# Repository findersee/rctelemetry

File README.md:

# rctelemetry
<p>FrSky Smart port compatible Telemetry board.</p>

Telemetry features:<ul>
<li>Two DC power measurement channels, current and Voltage for speed controllers.</li>
<li>Battery input voltage measurement</li>
</ul>
Sbus integration:<ul>
  <li>2 servo channels</li>
  <li>2 PWM capable output channels 10A each</li>
  <li>2 PWM capable output channels 4A each</li>
  <li>2 Digital output channels 4A each</li>
  <li>2 Opto-isolated inputs</li>
  <li> Expansion UART </li>
</ul>

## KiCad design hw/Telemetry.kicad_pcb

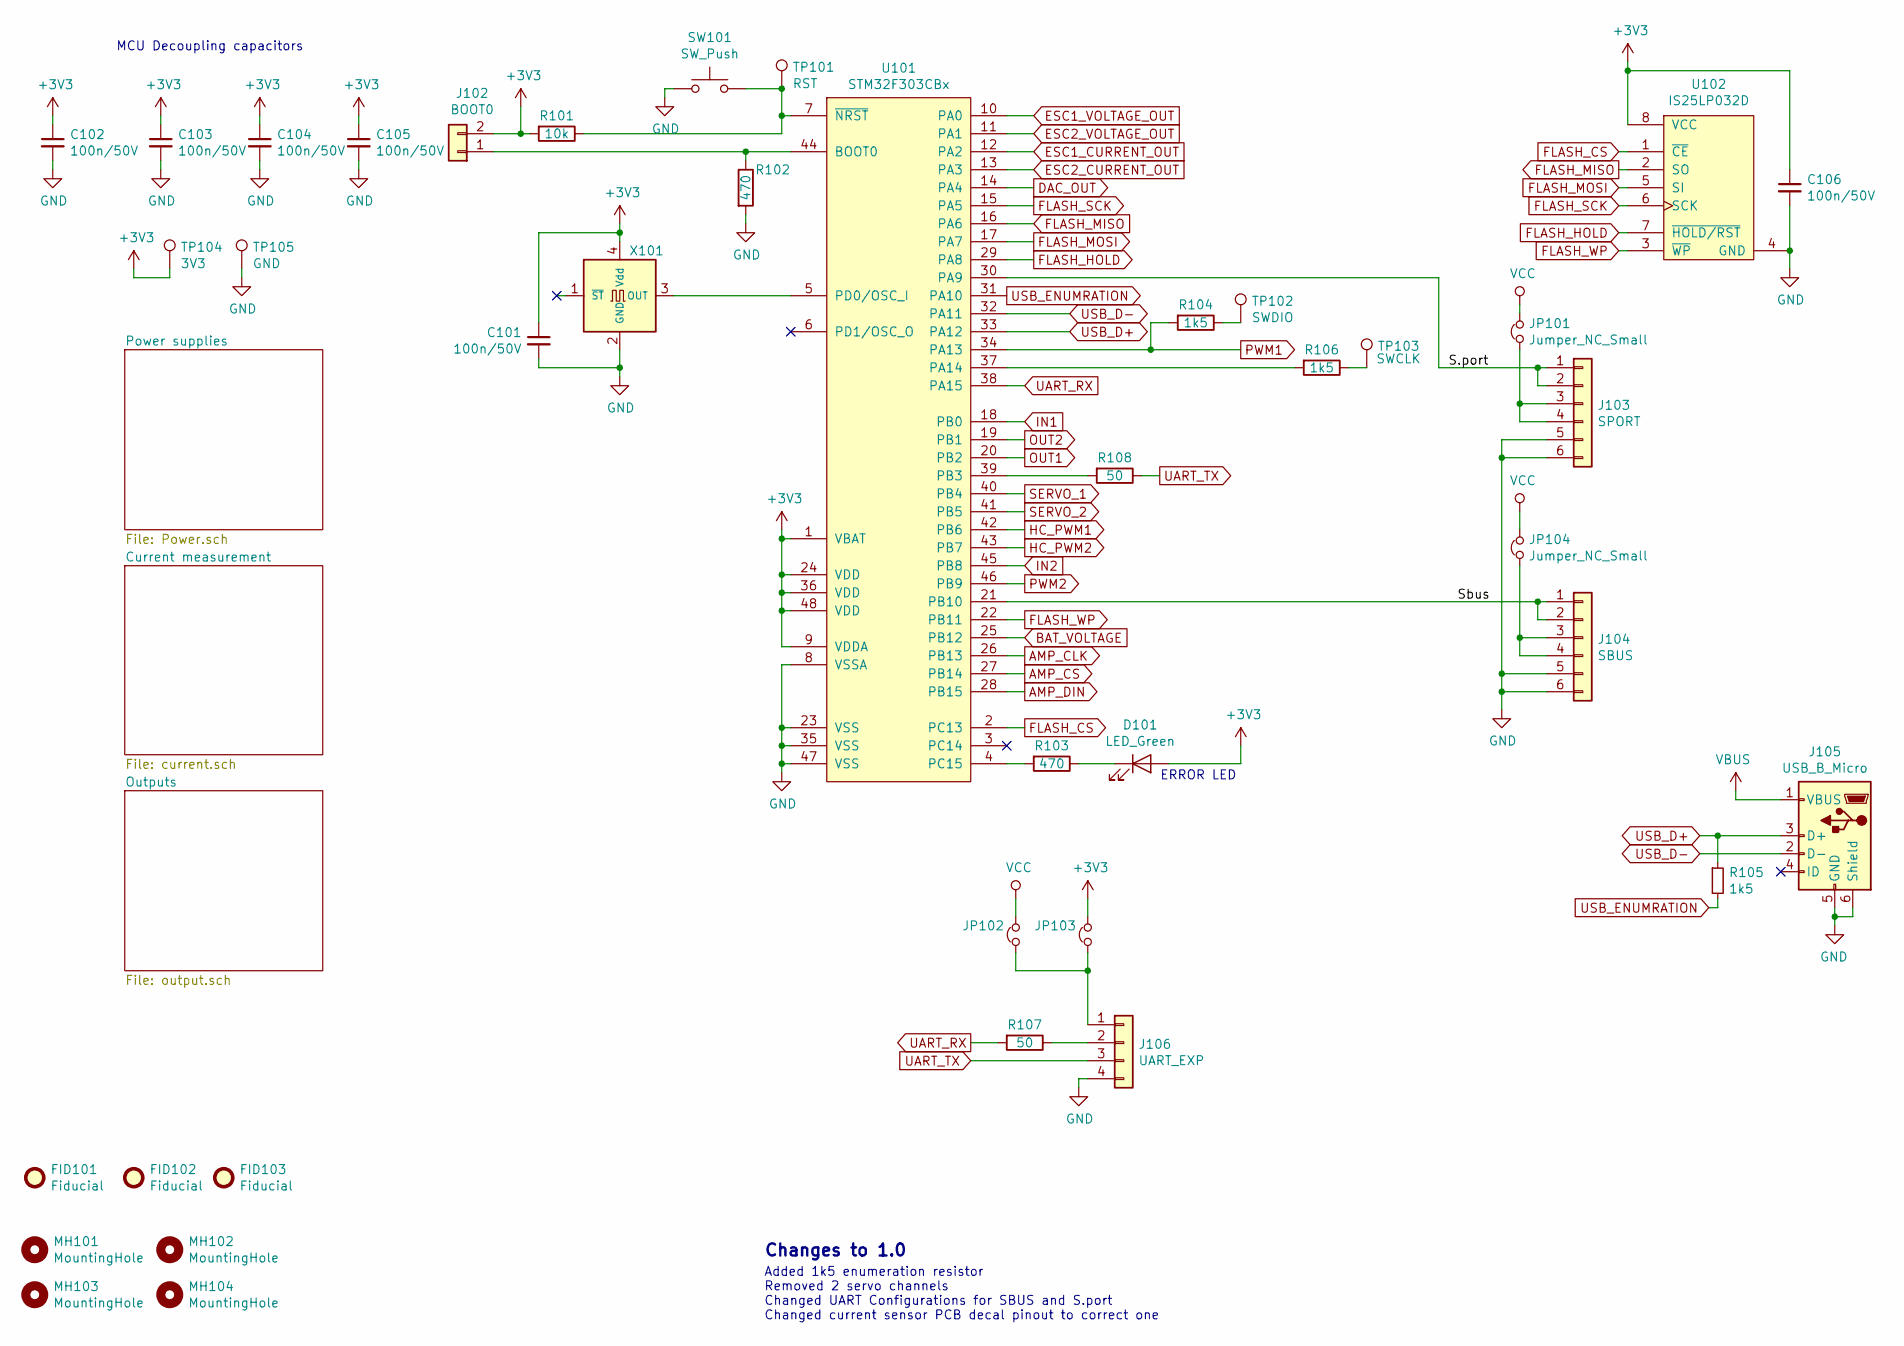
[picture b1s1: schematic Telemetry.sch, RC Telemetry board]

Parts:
C101, C102, C103, C104, C105, C106: 100n/50V; C_0603_1608Metric_Pad1.05x0.95mm_HandSolder
D101: LED_Green; LED_0603_HandSoldering
FID101, FID102, FID103: Fiducial; Fiducial_1mm_Mask2mm
J102: BOOT0; Pin_Header_Straight_1x02_Pitch1.27mm
J103: SPORT; Pin_Header_Straight_2x03
J104: SBUS; Pin_Header_Straight_2x03
J105: USB_B_Micro; USB_Micro-B
J106: UART_EXP; PinHeader_2x02_P2.54mm_Vertical
JP101, JP104: Jumper_NC_Small; PinHeader_1x02_P1.27mm_Vertical
JP102, JP103: Jumper_NC_Small; R_0402_1005Metric
MH101, MH102, MH103, MH104: MountingHole; MountingHole_3.2mm_M3_DIN965
R101: 10k; R_0603_1608Metric_Pad1.05x0.95mm_HandSolder
R102, R103: 470; R_0603_1608Metric_Pad1.05x0.95mm_HandSolder
R104, R105, R106: 1k5; R_0603_1608Metric_Pad1.05x0.95mm_HandSolder
R107, R108: 50; R_0603_1608Metric_Pad1.05x0.95mm_HandSolder
SW101: SW_Push; SW_SPST_B3U-1000P; MPN B3U-1000P
TP101: RST; SolderWirePad_single_0-8mmDrill
TP102: SWDIO; SolderWirePad_single_0-8mmDrill
TP103: SWCLK; SolderWirePad_single_0-8mmDrill
TP104: 3V3; SolderWirePad_single_0-8mmDrill
TP105: GND; SolderWirePad_single_0-8mmDrill
U101: STM32F303CBx; LQFP-48_7x7mm_Pitch0.5mm; MPN STM32F303CB
U102: IS25LP032D; SOIC-8_W5.6mm; MPN IS25LP032D
X101: SG-310_SCF_8.000000MHZ; SG- 310; MPN SG-310_SCF_8.000000MHZ

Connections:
+3V3: C101.1, C102.1, C103.1, C104.1, C105.1, C106.1, D101.2 (A), J102.2, JP103.2, R101.2, TP104.1, U101.1 (VBAT), U101.9 (VDDA), U101.24 (VDD), U101.36 (VDD), U101.48 (VDD), U102.8 (VCC), X101.4 (Vdd); also elsewhere on the board
/S.port: J103.1, J103.2, U101.30 (PA9)
/Sbus: J104.1, J104.2, U101.21 (PB10)
AMP_CLK: U101.26 (PB13); also elsewhere on the board
AMP_CS: U101.27 (PB14); also elsewhere on the board
AMP_DIN: U101.28 (PB15); also elsewhere on the board
BAT_VOLTAGE: U101.25 (PB12); also elsewhere on the board
DAC_OUT: U101.14 (PA4); also elsewhere on the board
ESC1_CURRENT_OUT: U101.12 (PA2); also elsewhere on the board
ESC1_VOLTAGE_OUT: U101.10 (PA0); also elsewhere on the board
ESC2_CURRENT_OUT: U101.13 (PA3); also elsewhere on the board
ESC2_VOLTAGE_OUT: U101.11 (PA1); also elsewhere on the board
FLASH_CS: U101.2 (PC13), U102.1 (~CE)
FLASH_HOLD: U101.29 (PA8), U102.7 (~HOLD/RST)
FLASH_MISO: U101.16 (PA6), U102.2 (SO)
FLASH_MOSI: U101.17 (PA7), U102.5 (SI)
FLASH_SCK: U101.15 (PA5), U102.6 (SCK)
FLASH_WP: U101.22 (PB11), U102.3 (~WP)
GND: C101.2, C102.2, C103.2, C104.2, C105.2, C106.2, J103.5, J103.6, J104.5, J104.6, J105.5 (GND), J105.6 (Shield), J106.4, R102.2, SW101.1, TP105.1, U101.8 (VSSA), U101.23 (VSS), U101.35 (VSS), U101.47 (VSS), U102.4 (GND), X101.2 (GND); also elsewhere on the board
HC_PWM1: U101.42 (PB6); also elsewhere on the board
HC_PWM2: U101.43 (PB7); also elsewhere on the board
IN1: U101.18 (PB0); also elsewhere on the board
IN2: U101.45 (PB8); also elsewhere on the board
unnamed: D101.1 (K), R103.1
unnamed: J102.1, R102.1, U101.44 (BOOT0)
unnamed: J103.3, J103.4, JP101.1
unnamed: J104.3, J104.4, JP104.1
unnamed: J106.1, JP102.1, JP103.1
unnamed: J106.2, R107.1
unnamed: R101.1, SW101.2, TP101.1, U101.7 (~NRST)
unnamed: R103.2, U101.4 (PC15)
unnamed: R104.1, TP102.1
unnamed: R106.1, TP103.1
unnamed: R106.2, U101.37 (PA14)
unnamed: R108.2, U101.39 (PB3)
unnamed: U101.5 (PD0/OSC_I), X101.3 (OUT)
OUT1: U101.20 (PB2); also elsewhere on the board
OUT2: U101.19 (PB1); also elsewhere on the board
PWM1: R104.2, U101.34 (PA13); also elsewhere on the board
PWM2: U101.46 (PB9); also elsewhere on the board
SERVO_1: U101.40 (PB4); also elsewhere on the board
SERVO_2: U101.41 (PB5); also elsewhere on the board
UART_RX: R107.2, U101.38 (PA15)
UART_TX: J106.3, R108.1
USB_D+: J105.3 (D+), R105.1, U101.33 (PA12)
USB_D-: J105.2 (D-), U101.32 (PA11)
USB_ENUMRATION: R105.2, U101.31 (PA10)
VBUS: J105.1 (VBUS)
VCC: JP101.2, JP102.2, JP104.2; also elsewhere on the board

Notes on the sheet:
ERROR LED
Changes to 1.0
MCU Decoupling capacitors
Added 1k5 enumeration resistor Removed 2 servo channels Changed UART Configurations for SBUS and S.port Changed current sensor PCB decal pinout to correct one

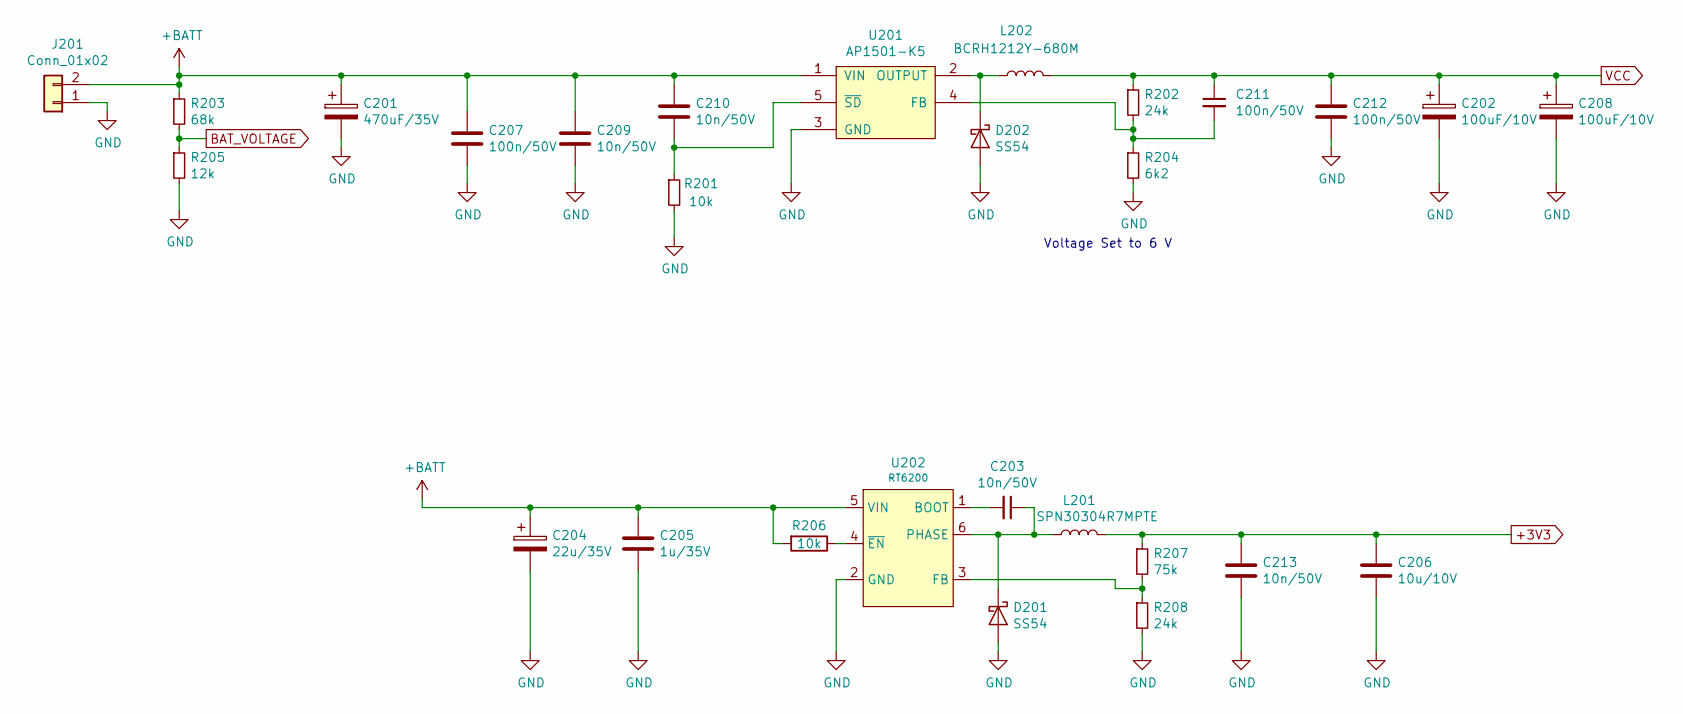
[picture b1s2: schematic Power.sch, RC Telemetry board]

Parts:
C201: 470uF/35V; CP_Radial_D10.0mm_P5.00mm
C202, C208: 100uF/10V; C_Radial_D7.5_L11.2_P2.5
C203, C213: 10n/50V; C_0603_1608Metric_Pad1.05x0.95mm_HandSolder
C204: 22u/35V; C_Radial_D7.5_L11.2_P2.5
C205: 1u/35V; C_0805_2012Metric_Pad1.15x1.40mm_HandSolder
C206: 10u/10V; C_0805_2012Metric_Pad1.15x1.40mm_HandSolder
C207, C211, C212: 100n/50V; C_0805_2012Metric_Pad1.15x1.40mm_HandSolder
C209, C210: 10n/50V; C_0805_2012Metric_Pad1.15x1.40mm_HandSolder
D201, D202: SS54; D_SMA_Handsoldering; MPN SS54
J201: Conn_01x02; 2Pin_4mm
L201: SPN30304R7MPTE; L_Sunlord_MWSA0402; MPN MWSA0402-4R7MT; LCSC Part-number C359291
L202: BCRH1212Y-680M; L_Sunlord_MWSA1206; MPN MWSA1206-470MT; LCSC Part-number C238002
R201, R206: 10k; R_0603_1608Metric_Pad1.05x0.95mm_HandSolder
R202, R208: 24k; R_0603_1608Metric_Pad1.05x0.95mm_HandSolder
R203: 68k; R_0603_1608Metric_Pad1.05x0.95mm_HandSolder
R204: 6k2; R_0603_1608Metric_Pad1.05x0.95mm_HandSolder
R205: 12k; R_0603_1608Metric_Pad1.05x0.95mm_HandSolder
R207: 75k; R_0603_1608Metric_Pad1.05x0.95mm_HandSolder
U201: AP1501-K5; TO-263-5_TabPin3; MPN AP1501-K5
U202: RT6200; SOT-23-6_Handsoldering; MPN RT6200

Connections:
+3V3: C206.1, C213.1, L201.2, R207.1; also elsewhere on the board
+BATT: C201.1, C204.1, C205.1, C207.1, C209.1, C210.1, J201.2, R203.1, R206.2, U201.1 (VIN), U202.5 (VIN); also elsewhere on the board
BAT_VOLTAGE: R203.2, R205.1; also elsewhere on the board
GND: C201.2, C202.2, C204.2, C205.2, C206.2, C207.2, C208.2, C209.2, C212.2, C213.2, D201.2 (A), D202.2 (A), J201.1, R201.2, R204.2, R205.2, R208.2, U201.3 (GND), U202.2 (GND); also elsewhere on the board
unnamed: C203.1, D201.1 (K), L201.1, U202.6 (PHASE)
unnamed: C203.2, U202.1 (BOOT)
unnamed: C210.2, R201.1, U201.5 (~SD)
unnamed: C211.2, R202.2, R204.1, U201.4 (FB)
unnamed: D202.1 (K), L202.1, U201.2 (OUTPUT)
unnamed: R206.1, U202.4 (~EN)
unnamed: R207.2, R208.1, U202.3 (FB)
VCC: C202.1, C208.1, C211.1, C212.1, L202.2, R202.1; also elsewhere on the board

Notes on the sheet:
Voltage Set to 6 V

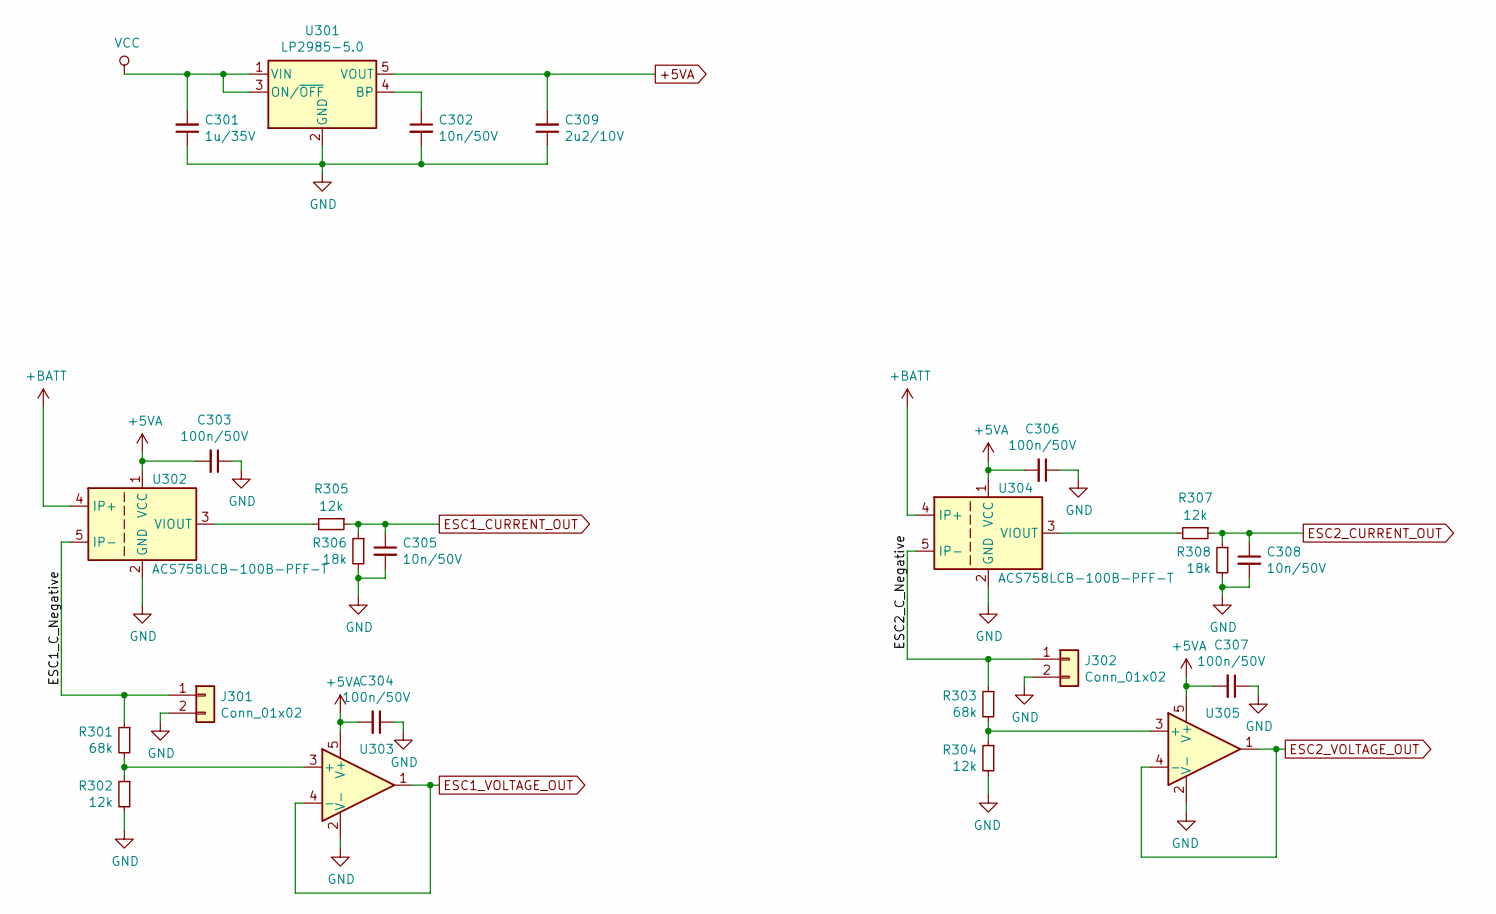
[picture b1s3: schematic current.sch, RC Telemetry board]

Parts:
C301: 1u/35V; C_0603_1608Metric_Pad1.05x0.95mm_HandSolder
C302, C305, C308: 10n/50V; C_0603_1608Metric_Pad1.05x0.95mm_HandSolder
C303, C304, C306, C307: 100n/50V; C_0603_1608Metric_Pad1.05x0.95mm_HandSolder
C309: 2u2/10V; C_0805_2012Metric_Pad1.15x1.40mm_HandSolder
J301, J302: Conn_01x02; 2Pin_4mm
R301, R303: 68k; R_0603_1608Metric_Pad1.05x0.95mm_HandSolder
R302, R304, R305, R307: 12k; R_0603_1608Metric_Pad1.05x0.95mm_HandSolder
R306, R308: 18k; R_0603_1608Metric_Pad1.05x0.95mm_HandSolder
U301: LP2985-5.0; SOT-23-5_HandSoldering; MPN LP2985-5.0
U302, U304: ACS758LCB-100B-PFF-T; Allegro_CB_PFF; MPN ACS758LCB-100B-PFF-T
U303, U305: MCP6001-OT; SOT-23-5_HandSoldering; MPN MCP6001-OT

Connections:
+5VA: C303.2, C304.2, C306.2, C307.2, C309.2, U301.5 (VOUT), U302.1 (VCC), U303.5 (V+), U304.1 (VCC), U305.5 (V+); also elsewhere on the board
+BATT: U302.4 (IP+), U304.4 (IP+); also elsewhere on the board
/Current measurement/ESC1_C_Negative: J301.1, R301.1, U302.5 (IP-)
/Current measurement/ESC2_C_Negative: J302.1, R303.1, U304.5 (IP-)
ESC1_CURRENT_OUT: C305.1, R305.1, R306.1; also elsewhere on the board
ESC1_VOLTAGE_OUT: U303.1, U303.4 (-); also elsewhere on the board
ESC2_CURRENT_OUT: C308.1, R307.1, R308.1; also elsewhere on the board
ESC2_VOLTAGE_OUT: U305.1, U305.4 (-); also elsewhere on the board
GND: C301.1, C302.2, C303.1, C304.1, C305.2, C306.1, C307.1, C308.2, C309.1, J301.2, J302.2, R302.2, R304.2, R306.2, R308.2, U301.2 (GND), U302.2 (GND), U303.2 (V-), U304.2 (GND), U305.2 (V-); also elsewhere on the board
unnamed: C302.1, U301.4 (BP)
unnamed: R301.2, R302.1, U303.3 (+)
unnamed: R303.2, R304.1, U305.3 (+)
unnamed: R305.2, U302.3 (VIOUT)
unnamed: R307.2, U304.3 (VIOUT)
VCC: C301.2, U301.1 (VIN), U301.3 (ON/~OFF~); also elsewhere on the board

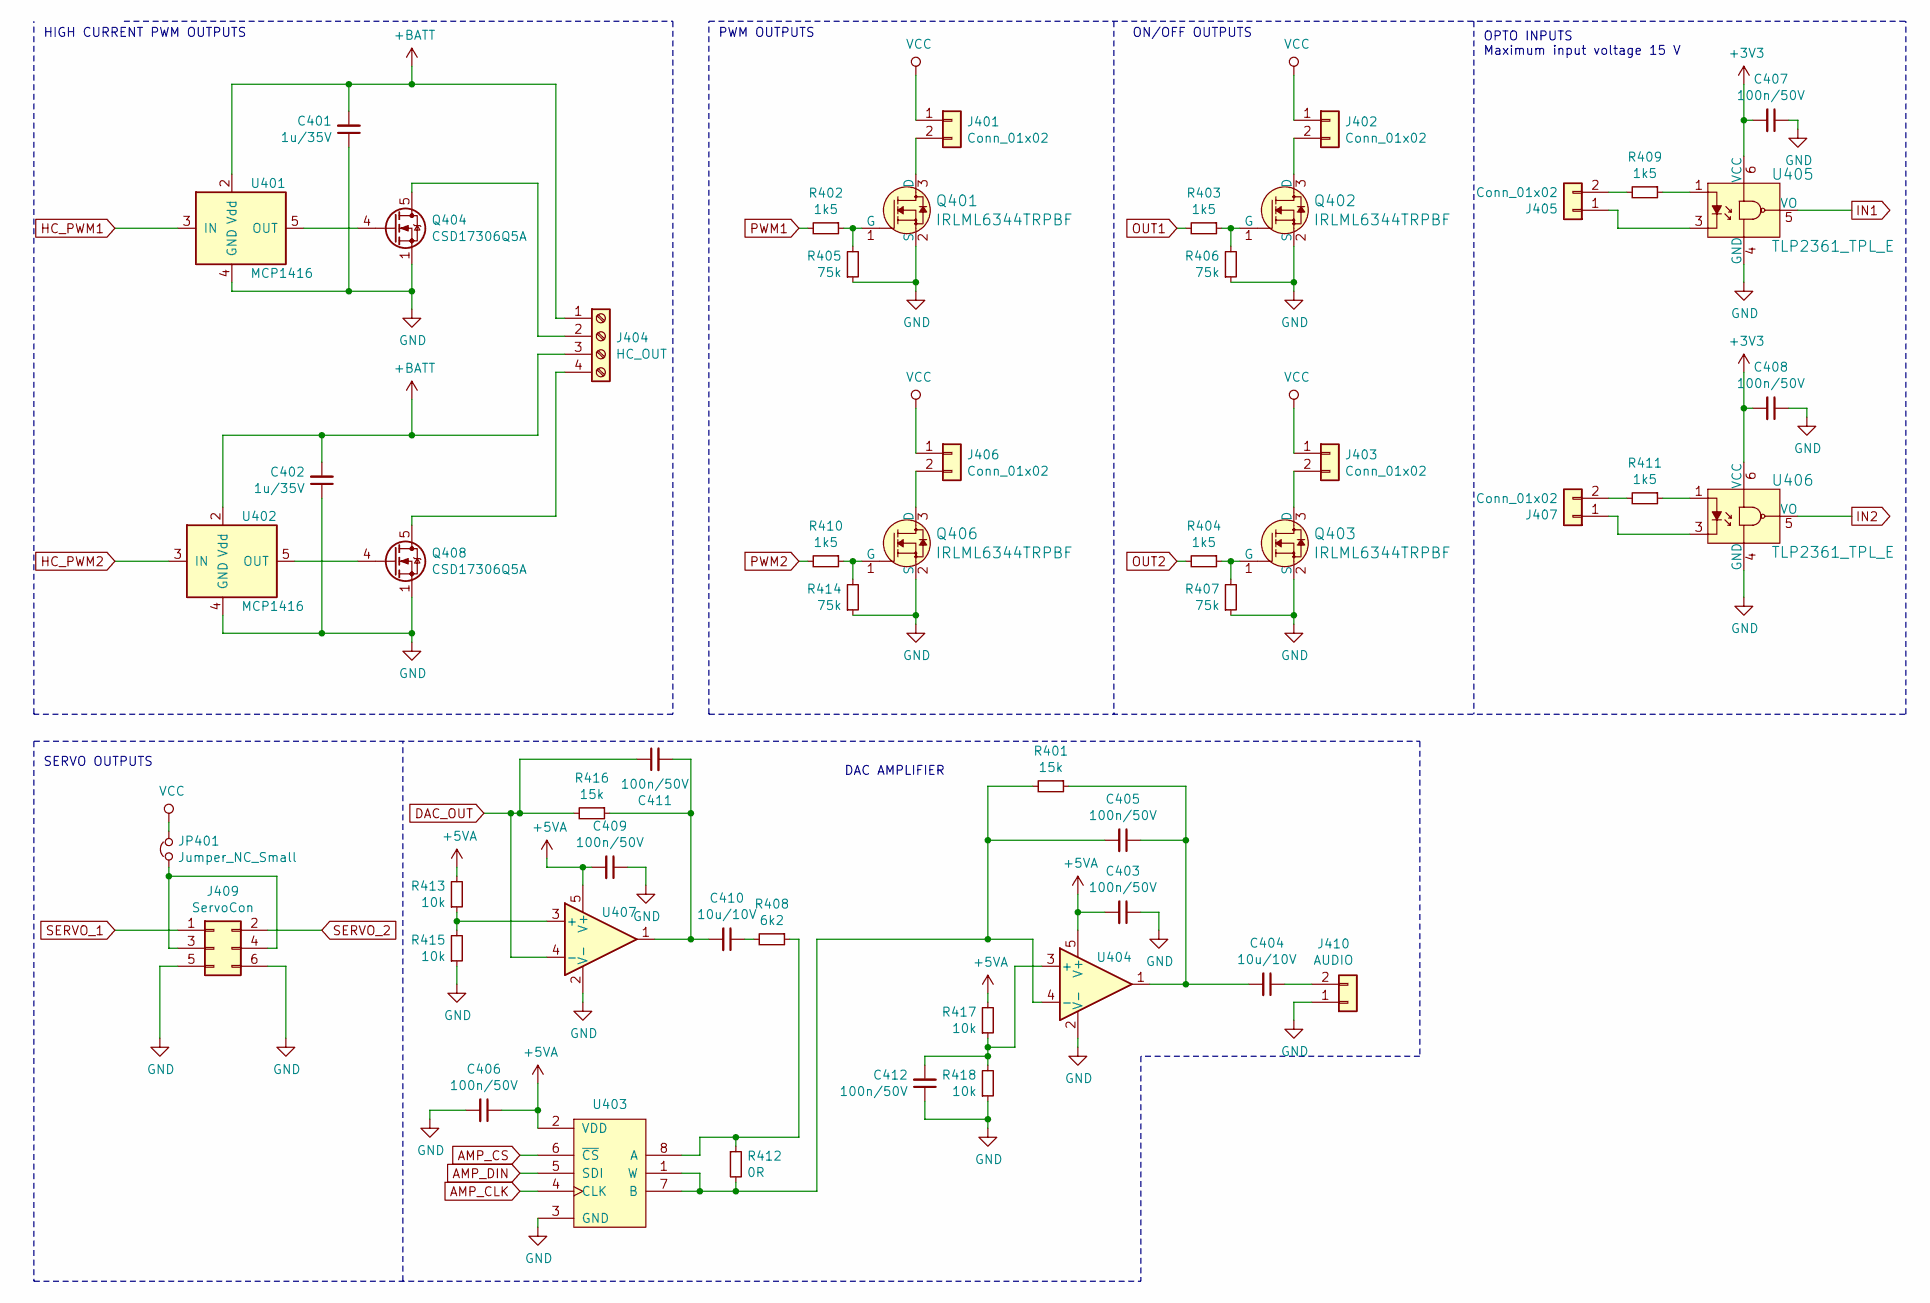
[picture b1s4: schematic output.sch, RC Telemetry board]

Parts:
C401, C402: 1u/35V; C_0805_2012Metric_Pad1.15x1.40mm_HandSolder
C403, C405, C406, C407, C408, C409, C411, C412: 100n/50V; C_0603_1608Metric_Pad1.05x0.95mm_HandSolder
C404, C410: 10u/10V; C_0603_1608Metric_Pad1.05x0.95mm_HandSolder
J401, J402, J403, J405, J406, J407: Conn_01x02; Molex_KK-254_AE-6410-02A_1x02_P2.54mm_Vertical
J404: HC_OUT; TerminalBlock_Phoenix_PT-1,5-4-5.0-H_1x04_P5.00mm_Horizontal
J409: ServoCon; PinHeader_2x03_P2.54mm_Vertical
J410: AUDIO; PinHeader_1x02_P2.54mm_Vertical
JP401: Jumper_NC_Small; PinHeader_1x02_P1.27mm_Vertical
Q401, Q402, Q403, Q406: IRLML6344TRPBF; SOT-23-3; MPN IRLML6344TRPBF; Digi-Key_PN IRLML6344TRPBFCT-ND
Q404, Q408: CSD17306Q5A; TDSON-8-1_HandSoldering; MPN CSD17306Q5A
R401, R416: 15k; R_0603_1608Metric_Pad1.05x0.95mm_HandSolder
R402, R403, R404, R409, R410, R411: 1k5; R_0603_1608Metric_Pad1.05x0.95mm_HandSolder
R405, R406, R407, R414: 75k; R_0603_1608Metric_Pad1.05x0.95mm_HandSolder
R408: 6k2; R_0603_1608Metric_Pad1.05x0.95mm_HandSolder
R412: 0R; R_0402_NoSilk
R413, R415, R417, R418: 10k; R_0603_1608Metric_Pad1.05x0.95mm_HandSolder
U401, U402: MCP1416; SOT-23-5_HandSoldering; MPN MCP1416
U403: AD5160BRJZ10-R2; SOT-23-8; MPN Analog Devices
U404, U407: MCP6001-OT; SOT-23-5_HandSoldering; MPN MCP6001-OT
U405, U406: TLP2361_TPL_E; SOIC-6-5_W4.55mm; MPN TLP2361-TPLECT; Digi-Key_PN TLP2361(TPLECT-ND

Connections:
+3V3: C407.2, C408.2, U405.6 (VCC), U406.6 (VCC); also elsewhere on the board
+5VA: C403.2, C406.1, C409.2, R413.2, R417.2, U403.2 (VDD), U404.5 (V+), U407.5 (V+); also elsewhere on the board
+BATT: C401.2, C402.2, J404.1, J404.3, U401.2 (Vdd), U402.2 (Vdd); also elsewhere on the board
AMP_CLK: U403.4 (CLK); also elsewhere on the board
AMP_CS: U403.6 (~CS); also elsewhere on the board
AMP_DIN: U403.5 (SDI); also elsewhere on the board
DAC_OUT: C411.1, R416.2, U407.4 (-); also elsewhere on the board
GND: C401.1, C402.1, C403.1, C406.2, C407.1, C408.1, C409.1, C412.1, J409.5, J409.6, J410.1, Q401.2 (S), Q402.2 (S), Q403.2 (S), Q404.1 (S), Q404.2 (S), Q404.3 (S), Q406.2 (S), Q408.1 (S), Q408.2 (S), Q408.3 (S), R405.1, R406.1, R407.1, R414.1, R415.1, R418.1, U401.4 (GND), U402.4 (GND), U403.3 (GND), U404.2 (V-), U405.4 (GND), U406.4 (GND), U407.2 (V-); also elsewhere on the board
HC_PWM1: U401.3 (IN); also elsewhere on the board
HC_PWM2: U402.3 (IN); also elsewhere on the board
IN1: U405.5 (VO); also elsewhere on the board
IN2: U406.5 (VO); also elsewhere on the board
unnamed: C404.1, J410.2
unnamed: C404.2, C405.1, R401.1, U404.1
unnamed: C405.2, R401.2, R412.2, U403.1 (W), U403.7 (B), U404.4 (-)
unnamed: C410.1, R408.2
unnamed: C410.2, C411.2, R416.1, U407.1
unnamed: C412.2, R417.1, R418.2, U404.3 (+)
unnamed: J401.2, Q401.3 (D)
unnamed: J402.2, Q402.3 (D)
unnamed: J403.2, Q403.3 (D)
unnamed: J404.2, Q404.5 (D)
unnamed: J404.4, Q408.5 (D)
unnamed: J405.1, U405.3
unnamed: J405.2, R409.2
unnamed: J406.2, Q406.3 (D)
unnamed: J407.1, U406.3
unnamed: J407.2, R411.2
unnamed: J409.3, J409.4, JP401.1
unnamed: Q401.1 (G), R402.1, R405.2
unnamed: Q402.1 (G), R403.1, R406.2
unnamed: Q403.1 (G), R404.1, R407.2
unnamed: Q404.4 (G), U401.5 (OUT)
unnamed: Q406.1 (G), R410.1, R414.2
unnamed: Q408.4 (G), U402.5 (OUT)
unnamed: R408.1, R412.1, U403.8 (A)
unnamed: R409.1, U405.1
unnamed: R411.1, U406.1
unnamed: R413.1, R415.2, U407.3 (+)
OUT1: R403.2; also elsewhere on the board
OUT2: R404.2; also elsewhere on the board
PWM1: R402.2; also elsewhere on the board
PWM2: R410.2; also elsewhere on the board
SERVO_1: J409.1; also elsewhere on the board
SERVO_2: J409.2; also elsewhere on the board
VCC: J401.1, J402.1, J403.1, J406.1, JP401.2; also elsewhere on the board

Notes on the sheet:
DAC AMPLIFIER
HIGH CURRENT PWM OUTPUTS
PWM OUTPUTS
ON/OFF OUTPUTS
SERVO OUTPUTS
OPTO INPUTS Maximum input voltage 15 V

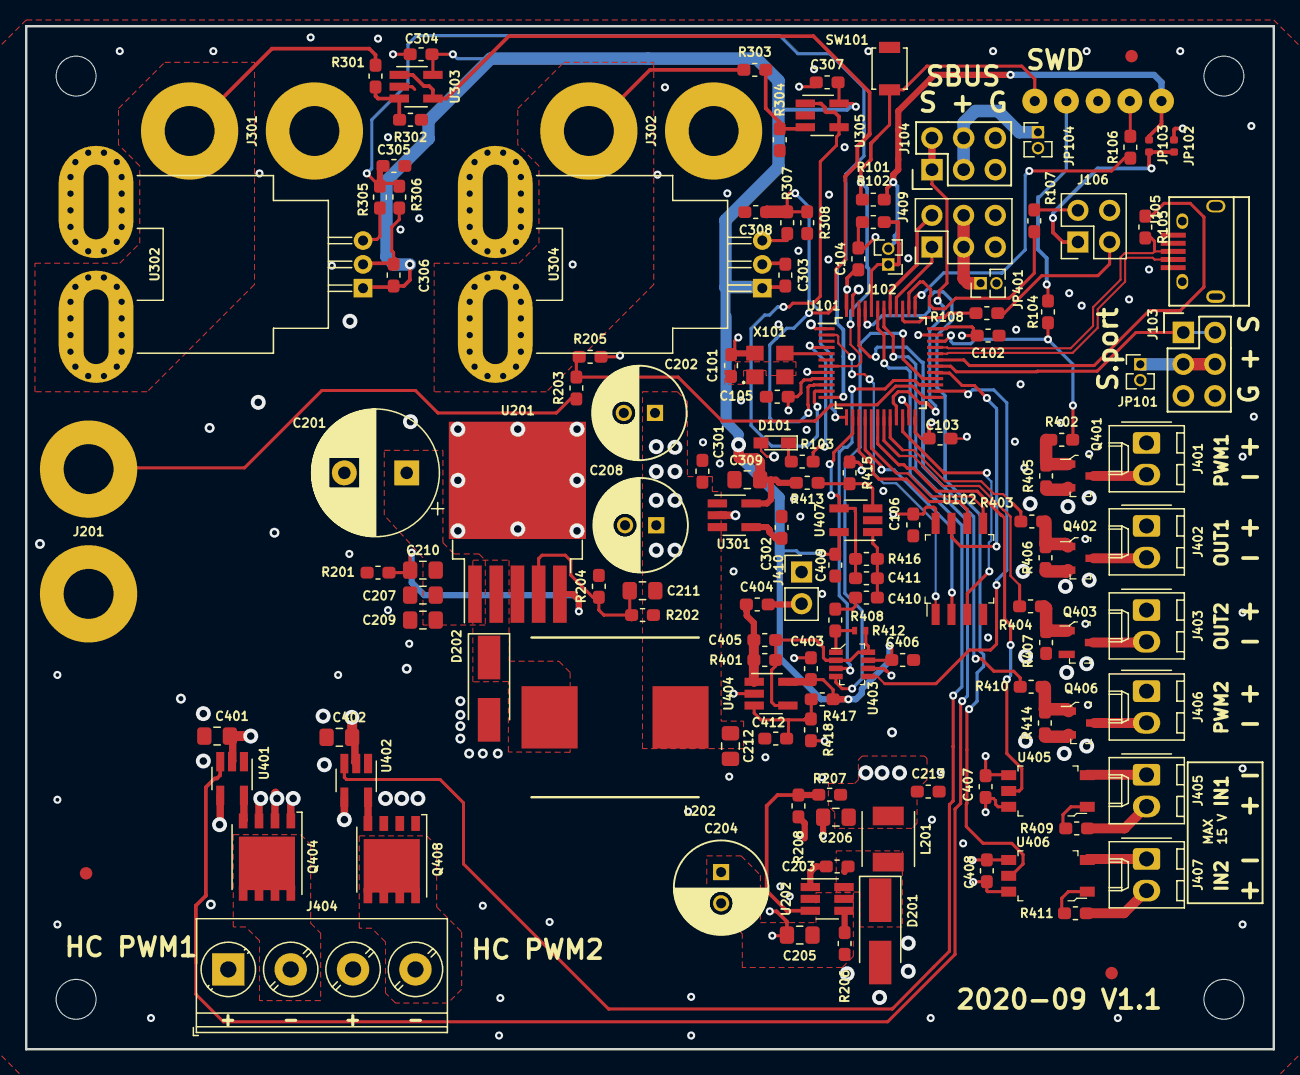
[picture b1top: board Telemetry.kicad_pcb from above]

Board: 4 copper layers, 100.0 x 82.0 mm, 146 parts (1 on the bottom side), 91 nets.

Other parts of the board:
https://github.com/findersee/rctelemetry: rctelemetry_QR

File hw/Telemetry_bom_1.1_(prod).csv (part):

Component,Description,Designator,Comment,Footprint,Quantity Per PCB,Datasheet,MPN,Manufacturer
1,"Unpolarized capacitor, small symbol",C101,100n/50V,0603_C,1,~,,
2,"Unpolarized capacitor, small symbol",C102,100n/50V,0603_C,1,~,,
3,"Unpolarized capacitor, small symbol",C103,100n/50V,0603_C,1,~,,
4,"Unpolarized capacitor, small symbol",C104,100n/50V,0603_C,1,~,,
5,"Unpolarized capacitor, small symbol",C105,100n/50V,0603_C,1,~,,
6,"Unpolarized capacitor, small symbol",C106,100n/50V,0603_C,1,~,,
7,Unpolarized capacitor,C207,100n/50V,0805_C,1,~,,
8,"Unpolarized capacitor, small symbol",C211,100n/50V,0805_C,1,~,,
9,Unpolarized capacitor,C212,100n/50V,0805_C,1,~,,
10,"Unpolarized capacitor, small symbol",C303,100n/50V,0603_C,1,~,,
11,"Unpolarized capacitor, small symbol",C304,100n/50V,0603_C,1,~,,
12,"Unpolarized capacitor, small symbol",C306,100n/50V,0603_C,1,~,,
13,"Unpolarized capacitor, small symbol",C307,100n/50V,0603_C,1,~,,
14,"Unpolarized capacitor, small symbol",C403,100n/50V,0603_C,1,~,,
15,"Unpolarized capacitor, small symbol",C405,100n/50V,0603_C,1,~,,
16,"Unpolarized capacitor, small symbol",C406,100n/50V,0603_C,1,~,,
17,"Unpolarized capacitor, small symbol",C407,100n/50V,0603_C,1,~,,
18,"Unpolarized capacitor, small symbol",C408,100n/50V,0603_C,1,~,,
19,"Unpolarized capacitor, small symbol",C409,100n/50V,0603_C,1,~,,
20,"Unpolarized capacitor, small symbol",C411,100n/50V,0603_C,1,~,,
21,"Unpolarized capacitor, small symbol",C412,100n/50V,0603_C,1,~,,
22,"Unpolarized capacitor, small symbol",C203,10n/50V,0603_C,1,~,,
23,Unpolarized capacitor,C209,10n/50V,0805_C,1,~,,
24,Unpolarized capacitor,C210,10n/50V,0805_C,1,~,,
25,Unpolarized capacitor,C213,10n/50V,0603_C,1,~,,
26,"Unpolarized capacitor, small symbol",C302,10n/50V,0603_C,1,~,,
27,Unpolarized capacitor,C206,10u/10V,0805_C,1,~,,
28,"Unpolarized capacitor, small symbol",C404,10u/10V,0603_C,1,~,,
29,"Unpolarized capacitor, small symbol",C410,10u/10V,0603_C,1,~,,
30,Unpolarized capacitor,C205,1u/35V,0805_C,1,~,,
31,"Unpolarized capacitor, small symbol",C301,1u/35V,0603_C,1,~,,
32,"Unpolarized capacitor, small symbol",C401,1u/35V,0805_C,1,~,,
33,"Unpolarized capacitor, small symbol",C402,1u/35V,0805_C,1,~,,
34,"Unpolarized capacitor, small symbol",C309,2u2/10V,0805_C,1,~,,
35,Light emitting diode,D101,LED_Green,LED_0603_HandSoldering,1,~,,
36,Schottky diode,D201,SS54,D_SMA,1,https://www.farnell.com/datasheets/1441695.pdf,SS54,
37,Schottky diode,D202,SS54,D_SMA,1,https://www.farnell.com/datasheets/1441695.pdf,SS54,
38,Inductor,L202, BCRH1212Y-680M,L_Sunlord_MWSA1206,1,https://datasheet.lcsc.com/szlcsc/Sunlord-MWSA1206-470MT_C11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,MWSA1206-470MT,Sunlord
39,Inductor,L201, SPN30304R7MPTE,L_Sunlord_MWSA0402,1,https://datasheet.lcsc.com/szlcsc/Sunlord-MWSA0402-4R7MT_C13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,MWSA0402-4R7MT,Sunlord
40,"100A Id, 30V Vds, NexFET N-Channel Power MOSFET, 4.2mOhm Ron, Qg (typ) 11.8nC, SON8 5x6mm",Q404,CSD17306Q5A,TDSON-8-1_HandSoldering,1,http://www.ti.com/lit/gpn/csd17306q5a,CSD17306Q5A,Texas Instruments
41,"100A Id, 30V Vds, NexFET N-Channel Power MOSFET, 4.2mOhm Ron, Qg (typ) 11.8nC, SON8 5x6mm",Q408,CSD17306Q5A,TDSON-8-1_HandSoldering,1,http://www.ti.com/lit/gpn/csd17306q5a,CSD17306Q5A,Texas Instruments
42,MOSFET N-CH 30V 5A SOT23,Q401,IRLML6344TRPBF,SOT-23-3,1,https://www.infineon.com/dgdl/irlml6344pbf.pdf?fileId=5546d4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,IRLML6344TRPBF,Infineon Technologies
43,MOSFET N-CH 30V 5A SOT23,Q402,IRLML6344TRPBF,SOT-23-3,1,https://www.infineon.com/dgdl/irlml6344pbf.pdf?fileId=5546d4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,IRLML6344TRPBF,Infineon Technologies
44,MOSFET N-CH 30V 5A SOT23,Q403,IRLML6344TRPBF,SOT-23-3,1,https://www.infineon.com/dgdl/irlml6344pbf.pdf?fileId=5546d4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,IRLML6344TRPBF,Infineon Technologies
45,MOSFET N-CH 30V 5A SOT23,Q406,IRLML6344TRPBF,SOT-23-3,1,https://www.infineon.com/dgdl/irlml6344pbf.pdf?fileId=5546d4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,IRLML6344TRPBF,Infineon Technologies
46,Resistor,R101,10k,0603_R,1,~,,
47,"Resistor, small symbol",R201,10k,0603_R,1,~,,
48,Resistor,R206,10k,0603_R,1,~,,
49,"Resistor, small symbol",R413,10k,0603_R,1,~,,
50,"Resistor, small symbol",R415,10k,0603_R,1,~,,
51,"Resistor, small symbol",R417,10k,0603_R,1,~,,
52,"Resistor, small symbol",R418,10k,0603_R,1,~,,
53,"Resistor, small symbol",R205,12k,0603_R,1,~,,
54,"Resistor, small symbol",R302,12k,0603_R,1,~,,
55,"Resistor, small symbol",R304,12k,0603_R,1,~,,
56,"Resistor, small symbol",R305,12k,0603_R,1,~,,
57,"Resistor, small symbol",R307,12k,0603_R,1,~,,
58,"Resistor, small symbol",R401,15k,0603_R,1,~,,
59,"Resistor, small symbol",R416,15k,0603_R,1,~,,
60,"Resistor, small symbol",R306,18k,0603_R,1,~,,
61,"Resistor, small symbol",R308,18k,0603_R,1,~,,
62,"Resistor, small symbol",R105,1k5,0603_R,1,~,,
63,"Resistor, small symbol",R402,1k5,0603_R,1,~,,
64,"Resistor, small symbol",R403,1k5,0603_R,1,~,,
65,"Resistor, small symbol",R404,1k5,0603_R,1,~,,
66,"Resistor, small symbol",R409,1k5,0603_R,1,~,,
67,"Resistor, small symbol",R410,1k5,0603_R,1,~,,
68,"Resistor, small symbol",R411,1k5,0603_R,1,~,,
69,"Resistor, small symbol",R202,24k,0603_R,1,~,,
70,"Resistor, small symbol",R208,24k,0603_R,1,~,,
71,Resistor,R102,470R,0603_R,1,~,,
72,Resistor,R103,470R,0603_R,1,~,,
73,Resistor,R104,50R,0603_R,1,~,,
74,Resistor,R106,50R,0603_R,1,~,,
75,Resistor,R107,50R,0603_R,1,~,,
76,Resistor,R108,50R,0603_R,1,~,,
77,"Resistor, small symbol",R203,68k,0603_R,1,~,,
78,"Resistor, small symbol",R301,68k,0603_R,1,~,,
79,"Resistor, small symbol",R303,68k,0603_R,1,~,,
80,"Resistor, small symbol",R204,6k2,0603_R,1,~,,
81,"Resistor, small symbol",R408,6k2,0603_R,1,~,,
82,"Resistor, small symbol",R207,75k,0603_R,1,~,,
83,"Resistor, small symbol",R405,75k,0603_R,1,~,,
84,"Resistor, small symbol",R406,75k,0603_R,1,~,,
85,"Resistor, small symbol",R407,75k,0603_R,1,~,,
86,"Resistor, small symbol",R414,75k,0603_R,1,~,,
87,,U403,AD5160BRJZ10-R2,SOT-23-8,1,https://www.analog.com/media/en/technical-documentation/data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,Analog Devices,AD5160BRJZ10-R2
88,,U201,AP1501-K5,TO-263-5_TabPin3,1,https://www.diodes.com/assets/Datasheets/AP1501.pdf,AP1501-K5,Diodes Inc
89,,U102,IS25LP032D,SOIC-8_W5.6mm,1,http://www.issi.com/WW/pdf/25LP-WP032D.pdf,IS25LP032D,ISSI
90,"150mA 16V Low-noise Low-dropout Regulator With Shutdown, 5.0V output voltage, SOT-23-5",U301,LP2985-5.0,SOT-23-5,1,http://www.ti.com/lit/ds/symlink/lp2985.pdf,LP2985-5.0,Texas Instruments
91,,U401,MCP1416,SOT-23-5,1,http://ww1.microchip.com/downloads/en/DeviceDoc/20002092F.pdf,MCP1416,Microchip
92,,U402,MCP1416,SOT-23-5,1,http://ww1.microchip.com/downloads/en/DeviceDoc/20002092F.pdf,MCP1416,Microchip
93,"1MHz, Low-Power Op Amp, SOT-23-5",U303,MCP6001-OT,SOT-23-5,1,http://ww1.microchip.com/downloads/en/DeviceDoc/21733j.pdf,MCP6001-OT,Microchip
94,"1MHz, Low-Power Op Amp, SOT-23-5",U305,MCP6001-OT,SOT-23-5,1,http://ww1.microchip.com/downloads/en/DeviceDoc/21733j.pdf,MCP6001-OT,Microchip
95,"1MHz, Low-Power Op Amp, SOT-23-5",U404,MCP6001-OT,SOT-23-5,1,http://ww1.microchip.com/downloads/en/DeviceDoc/21733j.pdf,MCP6001-OT,Microchip
96,"1MHz, Low-Power Op Amp, SOT-23-5",U407,MCP6001-OT,SOT-23-5,1,http://ww1.microchip.com/downloads/en/DeviceDoc/21733j.pdf,MCP6001-OT,Microchip
97,,U202,RT6200,SOT-23-6_Handsoldering,1,https://www.richtek.com/assets/product_file/RT6200/DS6200-04.pdf,RT6200,Richtek Tech
98,,U101,STM32F303CBx,LQFP-48_7x7mm_Pitch0.5mm,1,https://www.st.com/resource/en/datasheet/stm32f303cb.pdf,STM32F303CB,ST Microelectronics
99,OPTOISO 3.75KV PSH PULL SO6-5,U405,TLP2361_TPL_E,SOIC-6-5_W4.55mm,1,https://toshiba.semicon-storage.com/info/docget.jsp?did=1422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,TLP2361-TPLECT,Toshiba Semiconductor and Storage
100,OPTOISO 3.75KV PSH PULL SO6-5,U406,TLP2361_TPL_E,SOIC-6-5_W4.55mm,1,https://toshiba.semicon-storage.com/info/docget.jsp?did=1422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,TLP2361-TPLECT,Toshiba Semiconductor and Storage
101,,X101,SG-310_SCF_8.000000MHZ,SG- 310,1,https://support.epson.biz/td/api/doc_check.php?dl=brief_SG-3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,SG-310_SCF_8.000000MHZ,Epson





Component Groups:,130
Component Count:,130
Fitted Components:,101
Number of PCBs:,1
Total components:,101
Schematic Version:,1.1
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
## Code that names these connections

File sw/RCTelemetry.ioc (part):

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Mcu.Name=STM32F303C(B-C)Tx
Mcu.Package=LQFP48
Mcu.UserName=STM32F303CCTx
PA0.GPIOParameters=GPIO_Label
PA0.GPIO_Label=ESC1 VOLTAGE
PA0.Mode=IN1-Single-Ended
PA0.Signal=ADC1_IN1
PA1.GPIOParameters=GPIO_Label
PA1.GPIO_Label=ESC2 VOLTAGE
PA1.Mode=IN2-Single-Ended
PA1.Signal=ADC1_IN2
PA10.GPIOParameters=GPIO_Label
PA10.GPIO_Label=USB_ENUMERATE
PA10.Signal=GPIO_Output
PA13.Mode=Serial_Wire
PA13.Signal=SYS_JTMS-SWDIO
PA14.Mode=Serial_Wire
PA14.Signal=SYS_JTCK-SWCLK
PA15.Mode=Asynchronous
PA15.Signal=USART2_RX
PA2.GPIOParameters=GPIO_Label
PA2.GPIO_Label=ESC1 CURRENT
PA2.Mode=IN3-Single-Ended
PA2.Signal=ADC1_IN3
PA3.GPIOParameters=GPIO_Label
PA3.GPIO_Label=ESC2 CURRENT
PA3.Mode=IN4-Single-Ended
PA3.Signal=ADC1_IN4
PA4.GPIOParameters=GPIO_Label
PA4.GPIO_Label=DAC_OUT
PA4.Signal=COMP_DAC1_group
PA5.GPIOParameters=GPIO_Label
PA5.GPIO_Label=FLASH_SCK
PA5.Mode=Full_Duplex_Master
PA5.Signal=SPI1_SCK
PA6.GPIOParameters=GPIO_Label
PA6.GPIO_Label=FLASH_MISO
PA6.Mode=Full_Duplex_Master
PA6.Signal=SPI1_MISO
PA7.GPIOParameters=GPIO_Label
PA7.GPIO_Label=FLASH_MOSI
PA7.Mode=Full_Duplex_Master
PA7.Signal=SPI1_MOSI
PA8.GPIOParameters=GPIO_Label
PA8.GPIO_Label=FLASH_HOLD
PA8.Signal=GPIO_Output
PA9.GPIOParameters=GPIO_PuPd,GPIO_Label,GPIO_ModeDefaultOD
PA9.GPIO_Label=Sport_UART
PA9.GPIO_ModeDefaultOD=GPIO_MODE_AF_PP
PA9.GPIO_PuPd=GPIO_NOPULL
PA9.Mode=Half_duplex(single_wire_mode)
PA9.Signal=USART1_TX
PB0.GPIOParameters=GPIO_PuPd,GPIO_Label
PB0.GPIO_Label=IN1
PB0.GPIO_PuPd=GPIO_PULLUP
PB0.Signal=GPIO_Input
PB1.GPIOParameters=GPIO_Label
PB1.GPIO_Label=OUT2
PB1.Signal=GPIO_Output
PB10.Mode=Half_duplex(single_wire_mode)
PB10.Signal=USART3_TX
PB11.GPIOParameters=GPIO_Label
PB11.GPIO_Label=FLASH_WP
PB11.Signal=GPIO_Output
PB12.GPIOParameters=GPIO_Label
PB12.GPIO_Label=BAT VOLTAGE
PB12.Mode=IN3-Single-Ended
PB12.Signal=ADC4_IN3
PB13.Mode=TX_Only_Simplex_Unidirect_Master
PB13.Signal=SPI2_SCK
PB14.GPIOParameters=GPIO_Label
PB14.GPIO_Label=AMP_CS
PB14.Signal=GPIO_Output
PB15.Mode=TX_Only_Simplex_Unidirect_Master
PB15.Signal=SPI2_MOSI
PB2.GPIOParameters=GPIO_Label
PB2.GPIO_Label=OUT1
PB2.Signal=GPIO_Output
PB3.Mode=Asynchronous
PB3.Signal=USART2_TX
PB4.GPIOParameters=GPIO_Label
PB4.GPIO_Label=Servo_2
PB4.Signal=S_TIM16_CH1
PB5.GPIOParameters=GPIO_Label
PB5.GPIO_Label=Servo_1
PB5.Signal=S_TIM17_CH1
PB6.GPIOParameters=GPIO_Label
PB6.GPIO_Label=HC OUT1
PB6.Signal=S_TIM4_CH1
PB7.GPIOParameters=GPIO_Label
PB7.GPIO_Label=HC OUT2
PB7.Signal=S_TIM4_CH2
PB8.GPIOParameters=GPIO_PuPd,GPIO_Label
PB8.GPIO_Label=IN2
PB8.GPIO_PuPd=GPIO_PULLUP
PB8.Signal=GPIO_Input
PB9.GPIOParameters=GPIO_Label
PB9.GPIO_Label=PWM2
PB9.Signal=S_TIM4_CH4
PC13.GPIOParameters=GPIO_Label,GPIO_ModeDefaultOutputPP
PC13.GPIO_Label=FLASH_CS
PC13.GPIO_ModeDefaultOutputPP=GPIO_MODE_OUTPUT_OD
PC13.Signal=GPIO_Output
PC15-OSC32_OUT.GPIOParameters=GPIO_Label
PC15-OSC32_OUT.GPIO_Label=ERROR_LED
PC15-OSC32_OUT.Signal=GPIO_Output
PF0-OSC_IN.Mode=HSE-External-Clock-Source
PF0-OSC_IN.Signal=RCC_OSC_IN
RCC.HSEPLLFreq_Value=8000000
RCC.HSE_VALUE=8000000
RCC.SYSCLKFreq_VALUE=48000000
RCC.SYSCLKSourceVirtual=RCC_SYSCLKSOURCE_PLLCLK
board=custom

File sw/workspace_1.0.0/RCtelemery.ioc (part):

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Mcu.Name=STM32F303C(B-C)Tx
Mcu.Package=LQFP48
Mcu.UserName=STM32F303CBTx
PA0.GPIOParameters=GPIO_Label
PA0.GPIO_Label=ESC1 VOLTAGE
PA0.Mode=IN1-Single-Ended
PA0.Signal=ADC1_IN1
PA1.GPIOParameters=GPIO_Label
PA1.GPIO_Label=ESC2 VOLTAGE
PA1.Mode=IN2-Single-Ended
PA1.Signal=ADC1_IN2
PA10.GPIOParameters=GPIO_Label
PA10.GPIO_Label=WP
PA10.Signal=GPIO_Output
PA11.Mode=Device
PA11.Signal=USB_DM
PA12.Mode=Device
PA12.Signal=USB_DP
PA13.GPIOParameters=GPIO_Label
PA13.GPIO_Label=PWM1
PA13.Signal=S_TIM4_CH3
PA14.GPIOParameters=GPIO_Label
PA14.GPIO_Label=Sbus_UART
PA14.Mode=Half_duplex(single_wire_mode)
PA14.Signal=USART2_TX
PA15.GPIOParameters=GPIO_Label
PA15.GPIO_Label=Servo 1
PA15.Signal=S_TIM2_CH1_ETR
PA2.GPIOParameters=GPIO_Label
PA2.GPIO_Label=ESC1 CURRENT
PA2.Mode=IN3-Single-Ended
PA2.Signal=ADC1_IN3
PA3.GPIOParameters=GPIO_Label
PA3.GPIO_Label=ESC2 CURRENT
PA3.Mode=IN4-Single-Ended
PA3.Signal=ADC1_IN4
PA4.GPIOParameters=GPIO_Label
PA4.GPIO_Label=DAC_OUT
PA4.Signal=COMP_DAC1_group
PA5.Mode=Full_Duplex_Master
PA5.Signal=SPI1_SCK
PA6.Mode=Full_Duplex_Master
PA6.Signal=SPI1_MISO
PA7.Mode=Full_Duplex_Master
PA7.Signal=SPI1_MOSI
PA8.GPIOParameters=GPIO_Label
PA8.GPIO_Label=SPI_CS
PA8.Signal=GPIO_Output
PA9.GPIOParameters=GPIO_Label
PA9.GPIO_Label=Sport_UART
PA9.Mode=Half_duplex(single_wire_mode)
PA9.Signal=USART1_TX
PB0.GPIOParameters=GPIO_Label
PB0.GPIO_Label=IN1
PB0.Signal=GPIO_Input
PB1.GPIOParameters=GPIO_Label
PB1.GPIO_Label=OUT2
PB1.Signal=GPIO_Output
PB10.Mode=Asynchronous
PB10.Signal=USART3_TX
PB11.Mode=Asynchronous
PB11.Signal=USART3_RX
PB12.GPIOParameters=GPIO_Label
PB12.GPIO_Label=BAT VOLTAGE
PB12.Mode=IN3-Single-Ended
PB12.Signal=ADC4_IN3
PB13.GPIOParameters=GPIO_Label
PB13.GPIO_Label=COOLING TEMP
PB13.Mode=IN5-Single-Ended
PB13.Signal=ADC3_IN5
PB14.GPIOParameters=GPIO_Label
PB14.GPIO_Label=Servo 4
PB14.Signal=S_TIM15_CH1
PB15.GPIOParameters=GPIO_Label
PB15.GPIO_Label=Servo 3
PB15.Signal=S_TIM15_CH2
PB2.GPIOParameters=GPIO_Label
PB2.GPIO_Label=OUT1
PB2.Signal=GPIO_Output
PB3.Mode=TX_Only_Simplex_Unidirect_Master
PB3.Signal=SPI3_SCK
PB4.GPIOParameters=GPIO_Label
PB4.GPIO_Label=Servo 2
PB4.Signal=S_TIM16_CH1
PB5.Mode=TX_Only_Simplex_Unidirect_Master
PB5.Signal=SPI3_MOSI
PB6.GPIOParameters=GPIO_Label
PB6.GPIO_Label=HC OUT1
PB6.Signal=S_TIM4_CH1
PB7.GPIOParameters=GPIO_Label
PB7.GPIO_Label=HC OUT2
PB7.Signal=S_TIM4_CH2
PB8.GPIOParameters=GPIO_Label
PB8.GPIO_Label=IN2
PB8.Signal=GPIO_Input
PB9.GPIOParameters=GPIO_Label
PB9.GPIO_Label=PWM2
PB9.Signal=S_TIM4_CH4
PC13.GPIOParameters=GPIO_Label
PC13.GPIO_Label=ERROR_LED
PC13.Signal=GPIO_Output
PC15-OSC32_OUT.GPIOParameters=GPIO_Label
PC15-OSC32_OUT.GPIO_Label=AMP_CS
PC15-OSC32_OUT.Signal=GPIO_Output
PF0-OSC_IN.Mode=HSE-External-Clock-Source
PF0-OSC_IN.Signal=RCC_OSC_IN
RCC.HSEPLLFreq_Value=8000000
RCC.HSE_VALUE=8000000
RCC.SYSCLKFreq_VALUE=48000000
RCC.SYSCLKSourceVirtual=RCC_SYSCLKSOURCE_PLLCLK
board=custom
